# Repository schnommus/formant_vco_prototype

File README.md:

# SMD Formant VCO Prototype
KiCAD files for eurorack-compatible formant-based VCO design. Mostly created just to learn KiCAD.

Video on construction/operation is here: https://www.youtube.com/watch?v=rq4ovZ2om6k

## ERRATA [V1A] (To be fixed in future revision)
- The TL071 op-amp in the CAD files is arbitrary, I actually used an LM358. Just use whatever 8-pin SOIC dual op-amp you like.
- Diodes (D1..) are incorrect footprint. Change this to suit.
- 10V reference chip, VCC is not connected to +V properly. This must be bridged.
- +/-15V designator actually should be +/-12V to match eurorack. Doesn't make any electrical difference, but it's what the schematic says.
- Be careful with tantalum capacitor orientation, check with schematic. Silkscreen 'line' is negative, not positive.

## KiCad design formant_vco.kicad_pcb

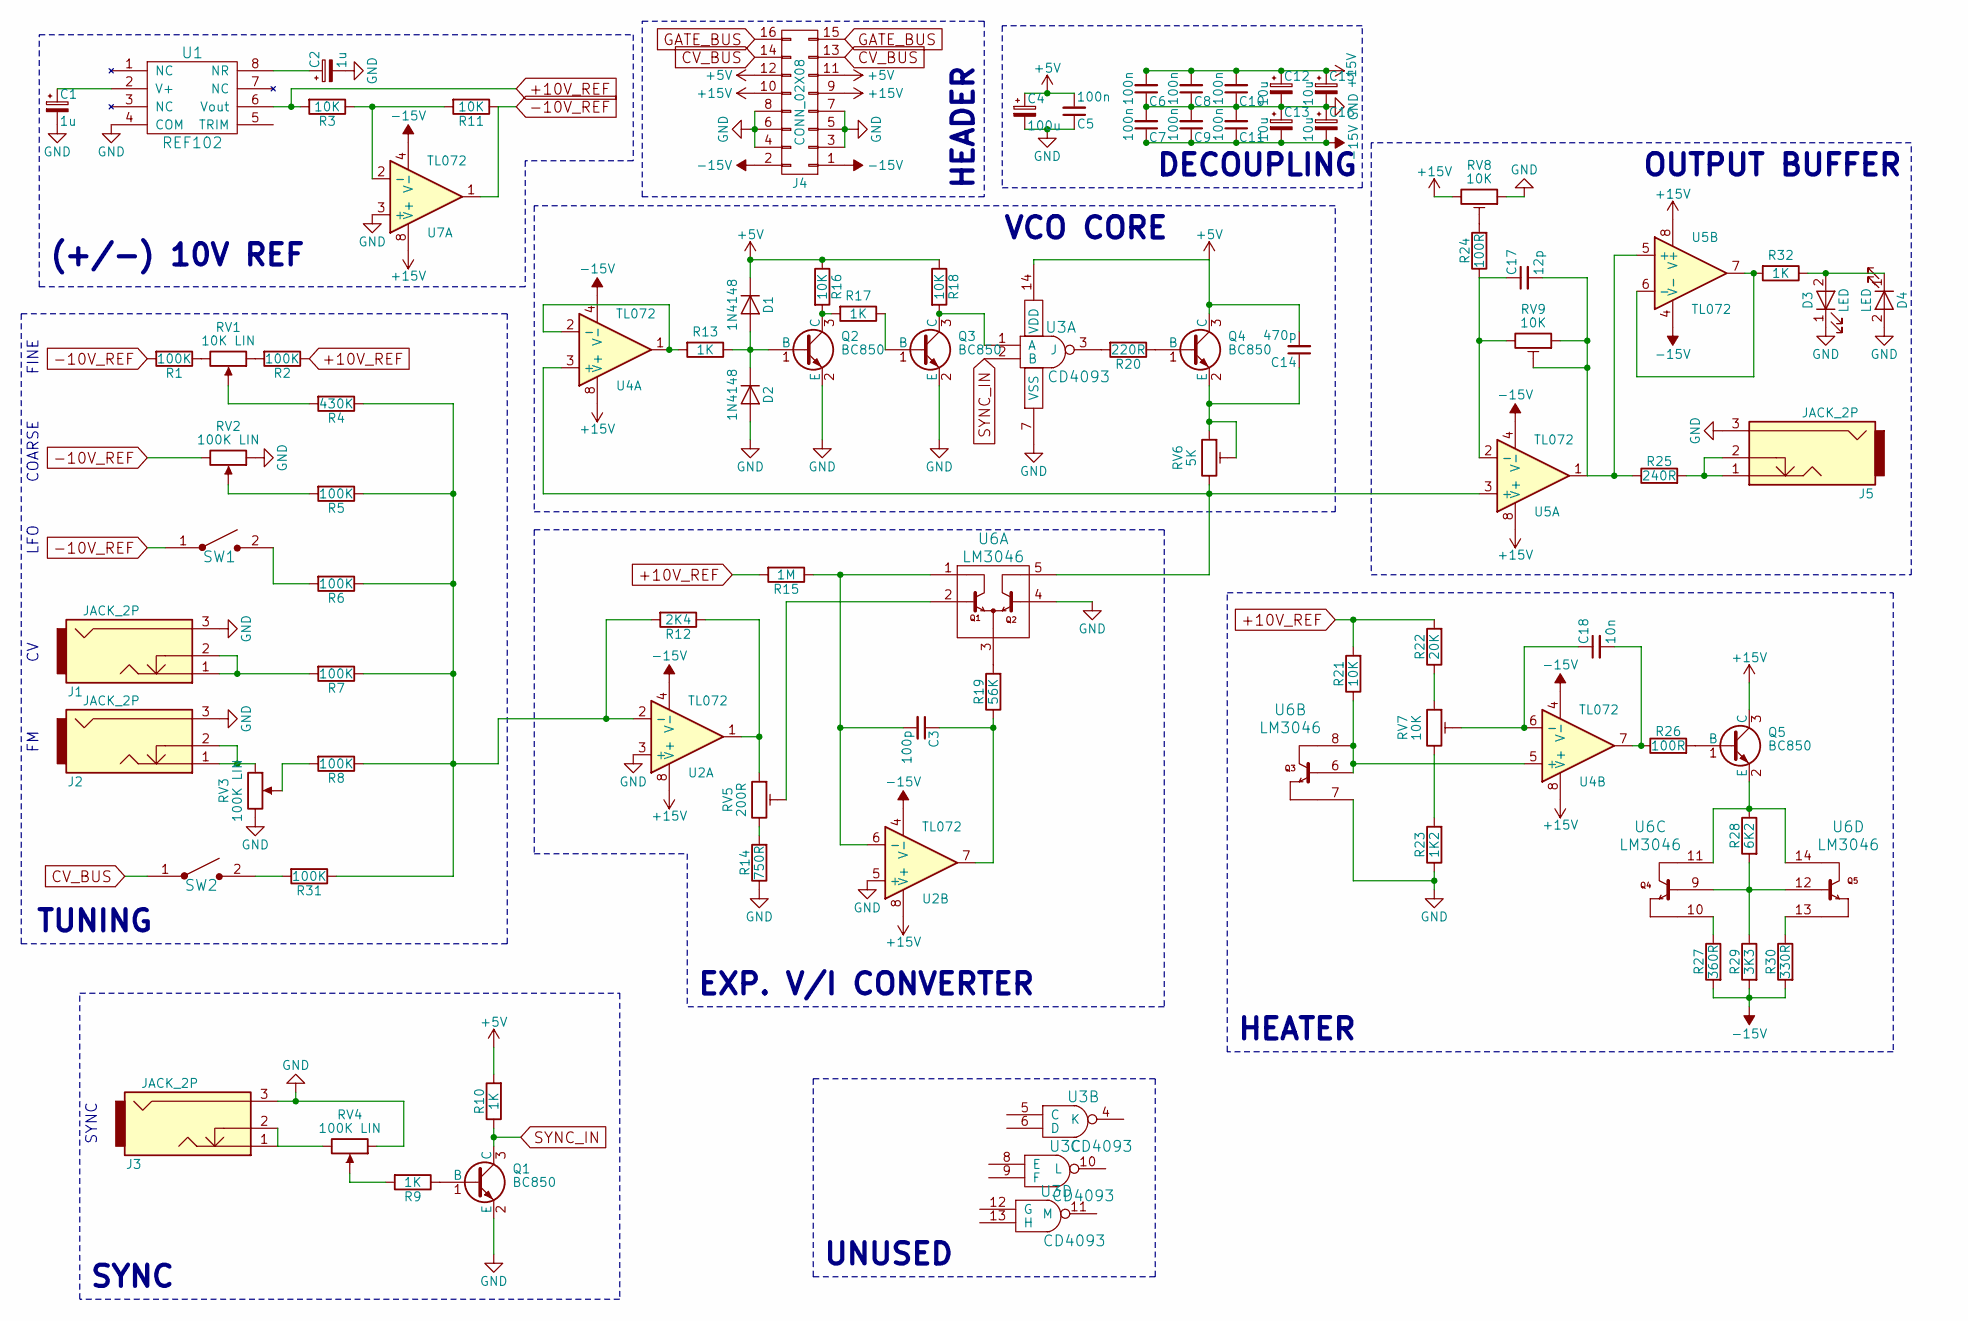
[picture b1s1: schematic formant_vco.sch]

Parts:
C1, C2: 1u; CP_Tantalum_Case-A_EIA-3216-18_Reflow
C3: 100p; C_0805
C4: 100u; CP_Tantalum_Case-A_EIA-3216-18_Reflow
C5, C6, C7, C8, C9, C10, C11: 100n; C_0805
C12, C13, C15, C16: 10u; CP_Tantalum_Case-A_EIA-3216-18_Reflow
C14: 470p; C_0805
C17: 12p; C_0805
C18: 10n; C_0805
D1, D2: 1N4148; D_0805
D3, D4: LED; LED_D5.0mm
J1, J2, J3, J5: JACK_2P; pj301bm
J4: CONN_02X08; IDC_Header_Straight_16pins
Q1, Q2, Q3, Q4, Q5: BC850; SOT-23
R1, R2, R5, R6, R7, R8, R31: 100K; R_0603
R3, R11, R16, R18, R21: 10K; R_0603
R4: 430K; R_0603
R9, R10, R13, R17, R32: 1K; R_0603
R12: 2K4; R_0603
R14: 750R; R_0603
R15: 1M; R_0603
R19: 56K; R_0603
R20: 220R; R_0603
R22: 20K; R_0603
R23: 1K2; R_0603
R24, R26: 100R; R_0603
R25: 240R; R_0603
R27: 360R; R_0603
R28: 6K2; R_0603
R29: 3K3; R_0603
R30: 330R; R_0603
RV1: 10K LIN; alpha_d_pot_vert
RV2, RV3, RV4: 100K LIN; alpha_d_pot_vert
RV5: 200R; bourns_trimmer_tc33x-2
RV6: 5K; bourns_trimmer_tc33x-2
RV7, RV8, RV9: 10K; bourns_trimmer_tc33x-2
SW1, SW2: SWITCH_SPST; Pin_Header_Straight_2x01_Pitch2.54mm
U1: REF102; SOIC-8_3.9x4.9mm_Pitch1.27mm
U2, U4, U5, U7: TL072; SOIC-8_3.9x4.9mm_Pitch1.27mm
U3: CD4093; SOIC-14_3.9x8.7mm_Pitch1.27mm
U6: LM3046; SOIC-14_3.9x8.7mm_Pitch1.27mm

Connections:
+5V: C4.1, C5.2, C14.2, D1.1 (K), J4.11, J4.12, Q4.3 (C), R10.2, R16.1, R18.1, U3.14 (VDD)
+10V_REF: R2.1, R3.2, R15.2, R21.2, R22.2, U1.6 (Vout)
+15V: C6.2, C8.2, C10.2, C12.1, C15.1, J4.9, J4.10, Q5.3 (C), RV8.3, U2.8 (V+), U4.8 (V+), U5.8 (V+), U7.8 (V+)
-10V_REF: R1.2, R11.1, RV2.3, SW1.1, U7.1
-15V: C7.1, C9.1, C11.1, C13.2, C16.2, J4.1, J4.2, R27.2, R29.2, R30.2, U2.4 (V-), U4.4 (V-), U5.4 (V-), U7.4 (V-)
CV_BUS: J4.13, J4.14, SW2.1
GATE_BUS: J4.15, J4.16
GND: C1.2, C2.2, C4.2, C5.1, C6.1, C7.2, C8.1, C9.2, C10.1, C11.2, C12.2, C13.1, C15.2, C16.1, D2.2 (A), D3.1 (K), D4.2 (A), J1.3, J2.3, J3.3, J4.3, J4.4, J4.5, J4.6, J4.7, J4.8, J5.3, Q1.2 (E), Q2.2 (E), Q3.2 (E), R14.1, R23.1, RV2.1, RV3.3, RV4.1, RV8.1, U1.4 (COM), U2.3 (+), U2.5 (+), U3.7 (VSS), U6.4, U6.7, U7.3 (+)
unnamed: C1.1, U1.2 (V+)
unnamed: C2.1, U1.8 (NR)
unnamed: C3.1, R19.1, U2.7
unnamed: C3.2, R15.1, U2.6 (-), U6.1
unnamed: C14.1, Q4.2 (E), RV6.1, RV6.2
unnamed: C17.1, R24.1, RV9.3, U5.2 (-)
unnamed: C17.2, R25.1, RV9.1, RV9.2, U5.1, U5.5 (+)
unnamed: C18.1, RV7.2, U4.6 (-)
unnamed: C18.2, R26.1, U4.7
unnamed: D1.2 (A), D2.1 (K), Q2.1 (B), R13.1
unnamed: D3.2 (A), D4.1 (K), R32.1
unnamed: J1.1, J1.2, R7.2
unnamed: J2.1, J2.2, RV3.1
unnamed: J3.1, J3.2, RV4.3
unnamed: J5.1, J5.2, R25.2
unnamed: Q1.1 (B), R9.1
unnamed: Q2.3 (C), R16.2, R17.2
unnamed: Q3.1 (B), R17.1
unnamed: Q3.3 (C), R18.2, U3.1 (A)
unnamed: Q4.1 (B), R20.1
unnamed: Q5.1 (B), R26.2
unnamed: Q5.2 (E), R28.1, U6.11, U6.14
unnamed: R1.1, RV1.3
unnamed: R2.2, RV1.1
unnamed: R4.2, RV1.2
unnamed: R5.2, RV2.2
unnamed: R6.2, SW1.2
unnamed: R8.2, RV3.2
unnamed: R9.2, RV4.2
unnamed: R3.1, R11.2, U7.2 (-)
unnamed: R12.1, RV5.1, U2.1
unnamed: R4.1, R5.1, R6.1, R7.1, R8.1, R12.2, R31.1, U2.2 (-)
unnamed: R13.2, U4.1, U4.2 (-)
unnamed: R14.2, RV5.3
unnamed: R19.2, U6.3
unnamed: R20.2, U3.3 (J)
unnamed: R21.1, U4.5 (+), U6.6, U6.8
unnamed: R22.1, RV7.1
unnamed: R23.2, RV7.3
unnamed: R24.2, RV8.2
unnamed: R27.1, U6.10
unnamed: R28.2, R29.1, U6.9, U6.12
unnamed: R30.1, U6.13
unnamed: R31.2, SW2.2
unnamed: R32.2, U5.6 (-), U5.7
unnamed: RV5.2, U6.2
unnamed: RV6.3, U4.3 (+), U5.3 (+), U6.5
SYNC_IN: Q1.3 (C), R10.1, U3.2 (B)

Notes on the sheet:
FINE
COARSE
LFO
SYNC
HEATER
UNUSED
TUNING
(+/-) 10V REF
OUTPUT BUFFER
VCO CORE
EXP. V/I CONVERTER
DECOUPLING
HEADER

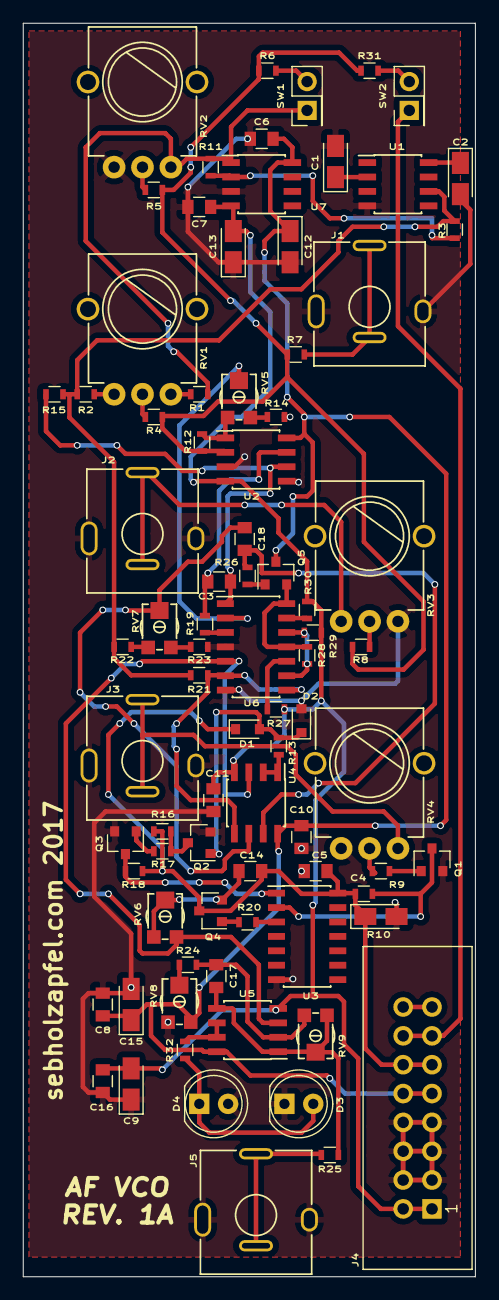
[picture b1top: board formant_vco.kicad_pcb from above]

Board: 2 copper layers, 39.8 x 110.4 mm, 82 parts (0 on the bottom side), 56 nets.

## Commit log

2017-07-15 Add eurorack synth power header
2017-07-15 Add output indicator LEDS
2017-07-16 Add footprints for mono jack and alpha pots
2017-07-16 Swap TL074 for TL072
2017-07-16 Start placing things
2017-07-16 place rest of components
2017-07-18 Some routing
2017-07-18 Final routing, fab outputs
